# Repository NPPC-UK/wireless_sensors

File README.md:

# wireless_sensors
Moteino based wireless sensors for measuring greenhouse temperature and light levels.

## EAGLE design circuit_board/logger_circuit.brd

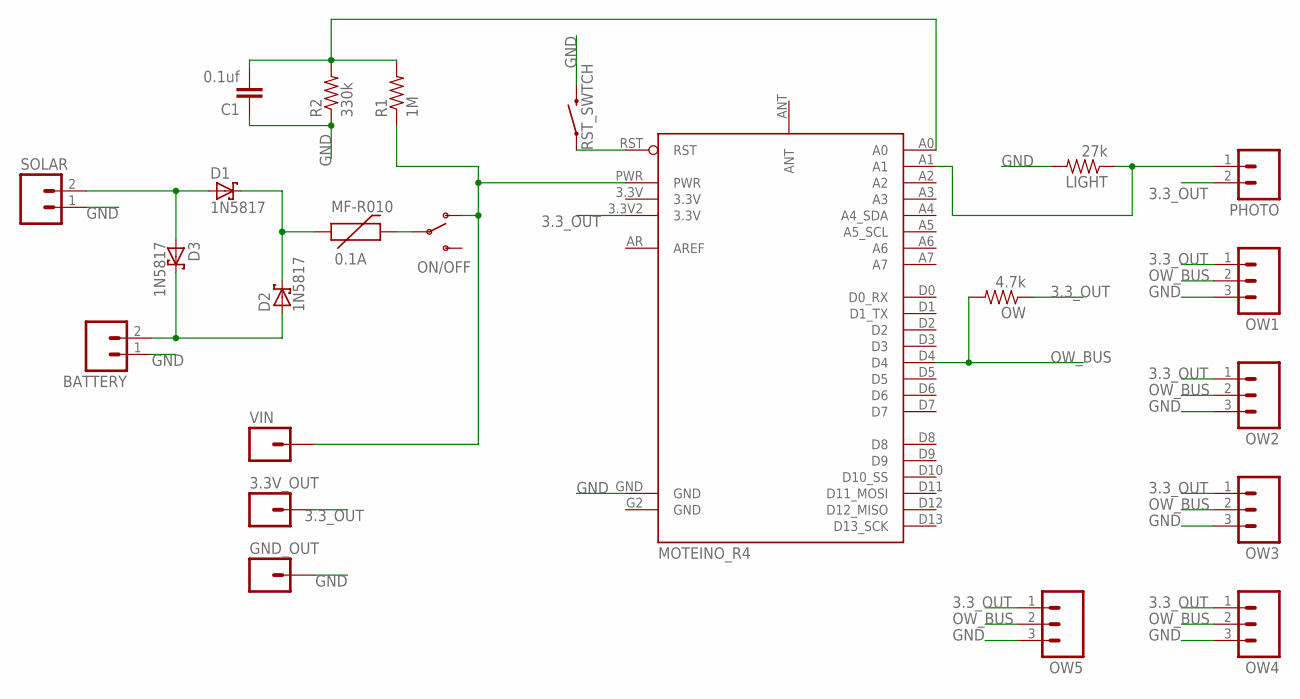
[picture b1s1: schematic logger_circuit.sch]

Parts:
3.3V_OUT: M01PTH; 1X01
BATTERY: M02JST-PTH-2; JST-2-PTH
C1: 0.1uf; CAP-PTH-5MM
D1, D2, D3: 1N5817; DO41-7.6
GND_OUT: M01PTH; 1X01
LIGHT: 27k; AXIAL-0.4
MF-R010: 0.1A; PTC
MOTEINO_R4: MOTEINO_R4_MODULEUSING_SQ_POST_PINS; MOTEINTO_R4_SQ
ON/OFF: SWITCH-SPDTPTH; SWITCH-SPDT
OW: 4.7k; AXIAL-0.4
OW1, OW2, OW3, OW4, OW5: M03JST-PTH-VERT; JST-3-PTH-VERT
PHOTO: M02JST-PTH-VERT; JST-2-PTH-VERT
R1: 1M; AXIAL-0.4
R2: 330k; AXIAL-0.4
RST_SWTCH: SWITCH-MOMENTARY-2PTH; TACTILE-PTH
SOLAR: M02JST-PTH-VERT; JST-2-PTH-VERT
VIN: M01PTH; 1X01

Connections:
3.3_OUT: 3.3V_OUT.1, MOTEINO_R4.3.3V2 (3.3V), OW.P$1 (1), OW1.1, OW2.1, OW3.1, OW4.1, OW5.1, PHOTO.2
GND: BATTERY.1, C1.1, GND_OUT.1, LIGHT.P$2 (2), MOTEINO_R4.G2 (GND), MOTEINO_R4.GND, OW1.3, OW2.3, OW3.3, OW4.3, OW5.3, R2.P$1 (1), RST_SWTCH.3 (2), SOLAR.1
unnamed: BATTERY.2, D2.A, D3.C
unnamed: D1.C, D2.C, MF-R010.P$1 (1)
unnamed: C1.2, MOTEINO_R4.A0, R1.P$2 (2), R2.P$2 (2)
unnamed: LIGHT.P$1 (1), MOTEINO_R4.A1, PHOTO.1
unnamed: D1.A, D3.A, SOLAR.2
unnamed: MOTEINO_R4.RST, RST_SWTCH.1
unnamed: MOTEINO_R4.PWR, ON/OFF.1 (O), R1.P$1 (1), VIN.1
unnamed: MF-R010.P$2 (2), ON/OFF.2
OW_BUS: MOTEINO_R4.D4, OW.P$2 (2), OW1.2, OW2.2, OW3.2, OW4.2, OW5.2

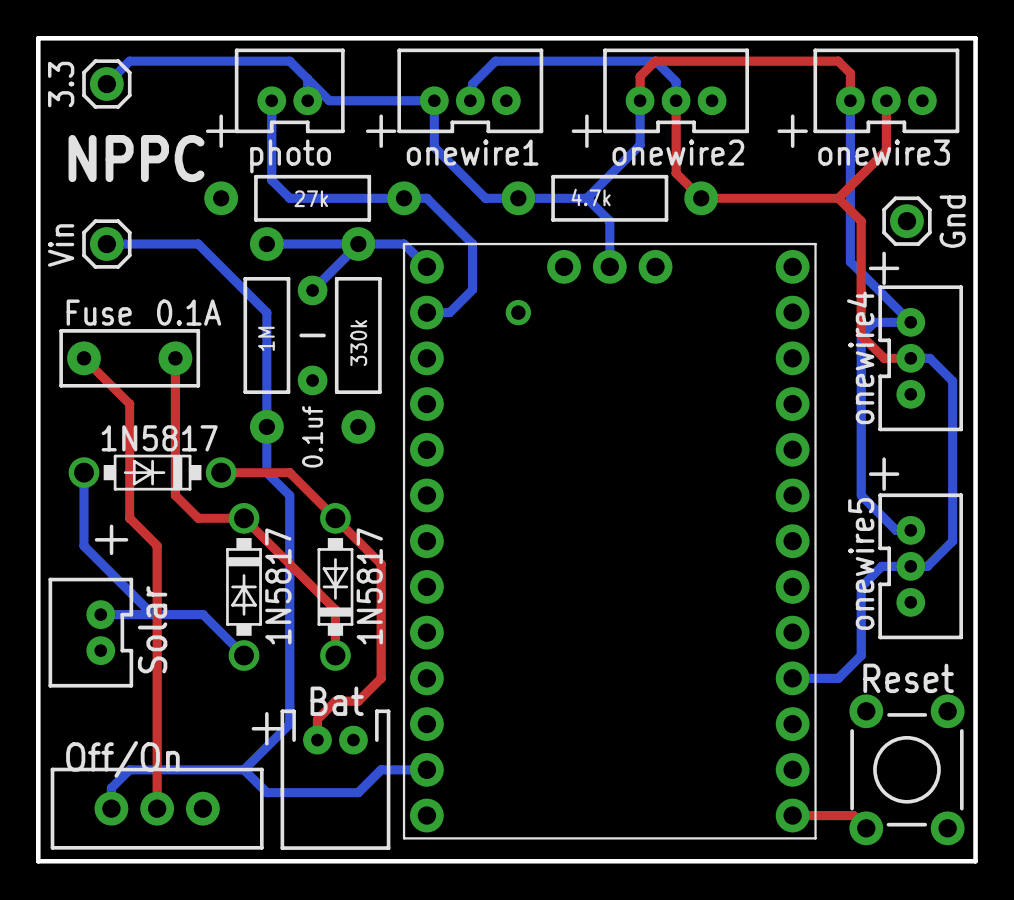
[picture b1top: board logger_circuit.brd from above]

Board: 2 copper layers, 52.1 x 45.7 mm, 23 parts (0 on the bottom side), 11 nets.

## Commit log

2017-02-19 Adding coordinator program
2017-02-19 Adding logger program
2017-02-19 Adding PCB designs
2017-02-20 Adding receiver and database setup files
2017-02-20 Adding logger setup files

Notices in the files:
parts and their libraries:
SparkFun-Resistors: Licensing: Creative Commons ShareAlike 4.0 International - https://creativecommons.org/licenses/by-sa/4.0
